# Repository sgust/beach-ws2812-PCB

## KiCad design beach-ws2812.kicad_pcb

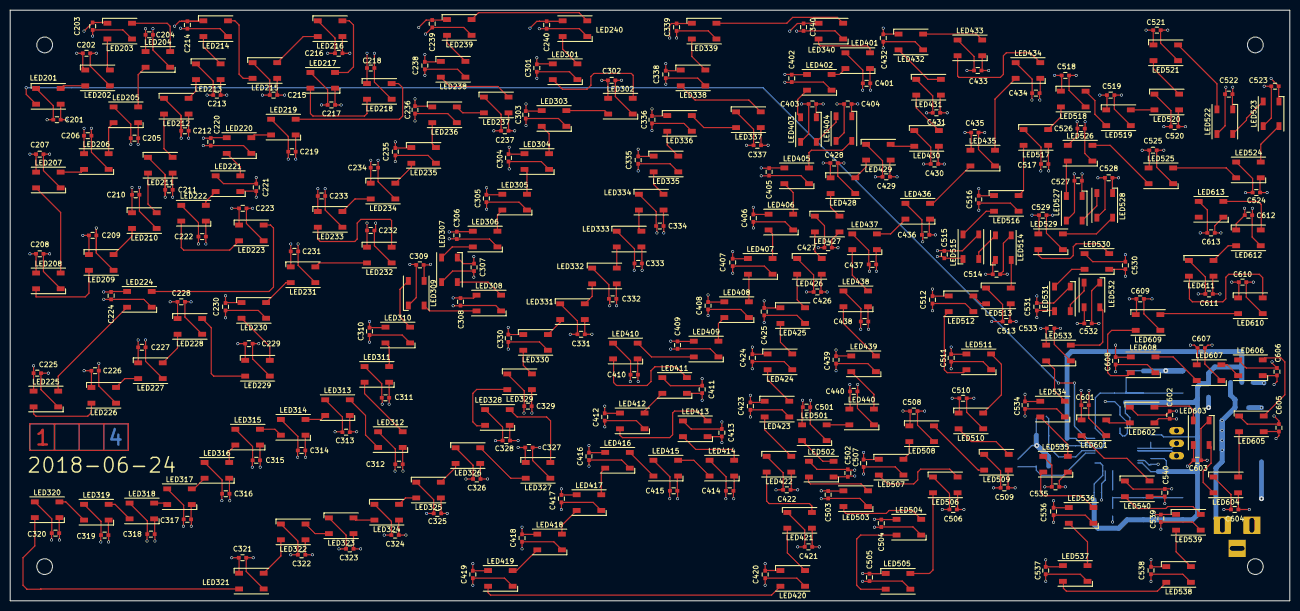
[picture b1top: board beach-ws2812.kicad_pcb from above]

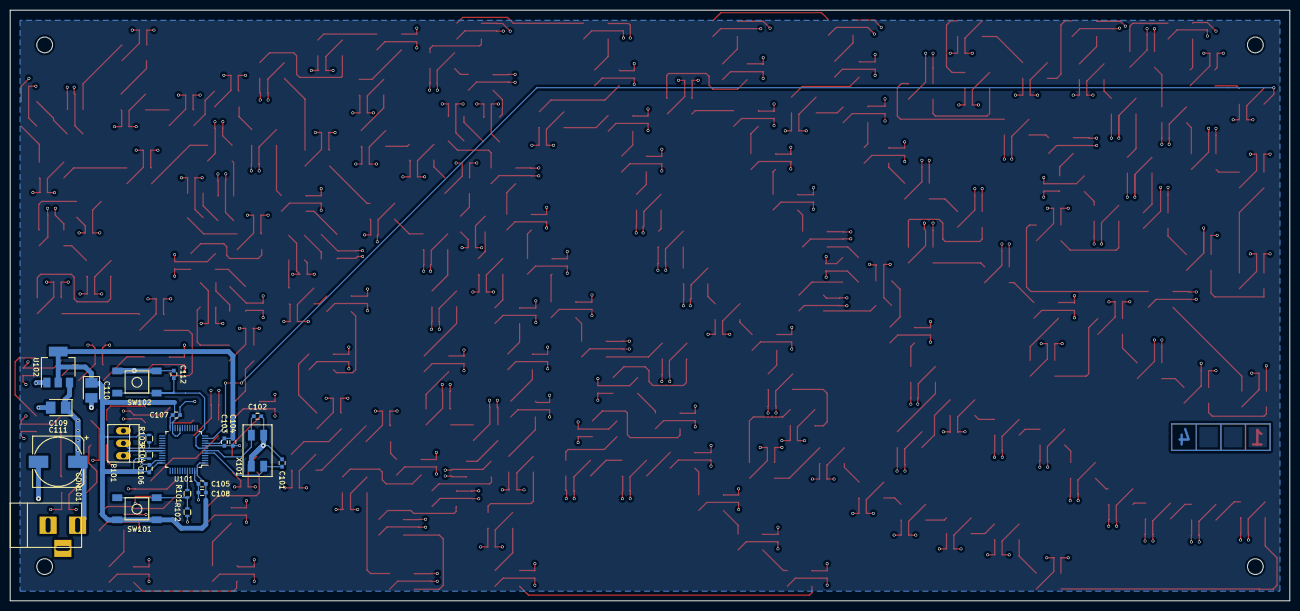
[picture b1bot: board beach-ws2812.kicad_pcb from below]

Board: 4 copper layers, 260.0 x 120.0 mm, 373 parts (23 on the bottom side), 183 nets.

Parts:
C101, C102: 15pF; C_0603
C103: 10nF; C_0603
C104: 1µF; C_0603
C105, C106, C107, C112, C201, C202, C203, C204, C205, C206, C207, C208, C209, C210, C211, C212, C213, C214, C215, C216, C217, C218, C219, C220, C221, C222, C223, C224, C225, C226, C227, C228, C229, C230, C231, C232, C233, C234, C235, C236, C237, C238, C239, C240, C301, C302, C303, C304, C305, C306, C307, C308, C309, C310, C311, C312, C313, C314, C315, C316, C317, C318, C319, C320, C321, C322, C323, C324, C325, C326, C327, C328, C329, C330, C331, C332, C333, C334, C335, C336, C337, C338, C339, C340, C401, C402, C403, C404, C405, C406, C407, C408, C409, C410, C411, C412, C413, C414, C415, C416, C417, C418, C419, C420, C421, C422, C423, C424, C425, C426, C427, C428, C429, C430, C431, C432, C433, C434, C435, C436, C437, C438, C439, C440, C501, C502, C503, C504, C505, C506, C507, C508, C509, C510, C511, C512, C513, C514, C515, C516, C517, C518, C519, C520, C521, C522, C523, C524, C525, C526, C527, C528, C529, C530, C531, C532, C533, C534, C535, C536, C537, C538, C539, C540, C601, C602, C603, C604, C605, C606, C607, C608, C609, C610, C611, C612, C613: 100nF; C_0603
C108: 4.7µF; C_0603
C109, C110: 10µF/16V; Tantalum_Case-B_EIA-3528-21_Reflow
C111: 1000µF/16V; c_elec_10x10
CON101: BARREL_JACK
HOLE1, HOLE2, HOLE3, HOLE4: MountingHole_3.2mm_M3
LED201, LED202, LED203, LED204, LED205, LED206, LED207, LED208, LED209, LED210, LED211, LED212, LED213, LED214, LED215, LED216, LED217, LED218, LED219, LED220, LED221, LED222, LED223, LED224, LED225, LED226, LED227, LED228, LED229, LED230, LED231, LED232, LED233, LED234, LED235, LED236, LED237, LED238, LED239, LED240, LED301, LED302, LED303, LED304, LED305, LED306, LED307, LED308, LED309, LED310, LED311, LED312, LED313, LED314, LED315, LED316, LED317, LED318, LED319, LED320, LED321, LED322, LED323, LED324, LED325, LED326, LED327, LED328, LED329, LED330, LED331, LED332, LED333, LED334, LED335, LED336, LED337, LED338, LED339, LED340, LED401, LED402, LED403, LED404, LED405, LED406, LED407, LED408, LED409, LED410, LED411, LED412, LED413, LED414, LED415, LED416, LED417, LED418, LED419, LED420, LED421, LED422, LED423, LED424, LED425, LED426, LED427, LED428, LED429, LED430, LED431, LED432, LED433, LED434, LED435, LED436, LED437, LED438, LED439, LED440, LED501, LED502, LED503, LED504, LED505, LED506, LED507, LED508, LED509, LED510, LED511, LED512, LED513, LED514, LED515, LED516, LED517, LED518, LED519, LED520, LED521, LED522, LED523, LED524, LED525, LED526, LED527, LED528, LED529, LED530, LED531, LED532, LED533, LED534, LED535, LED536, LED537, LED538, LED539, LED540, LED601, LED602, LED603, LED604, LED605, LED606, LED607, LED608, LED609, LED610, LED611, LED612, LED613: WS2812B; LED_WS2812B-PLCC4
P101: CONN_01X03; PINHEAD1-3
R101: 10K; R_0603
R102: 1K; R_0603
R103, R104: 100K; R_0603
SW101, SW102: Pushbutton; SMD_SWITCH_6x6_LSG
U101: STM32F103C(8-B)Tx; TQFP-48_7x7mm_Pitch0.5mm
U102: LM1117-3.3; SOT-223
X101: 8MHz; Euroquartz_MQ

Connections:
+3V3: C103.1, C104.1, C105.1, C106.1, C107.1, C108.1, C110.1, R103.1, R104.1, SW101.1, SW101.2, U101.1, U101.9, U101.24, U101.36, U101.48, U102.2, U102.4
+5V: C109.1, C111.1, C201.1, C202.1, C203.1, C204.1, C205.1, C206.1, C207.1, C208.1, C209.1, C210.1, C211.1, C212.1, C213.1, C214.1, C215.1, C216.1, C217.1, C218.1, C219.1, C220.1, C221.1, C222.1, C223.1, C224.1, C225.1, C226.1, C227.1, C228.1, C229.1, C230.1, C231.1, C232.1, C233.1, C234.1, C235.1, C236.1, C237.1, C238.1, C239.1, C240.1, C301.1, C302.1, C303.1, C304.1, C305.1, C306.1, C307.1, C308.1, C309.1, C310.1, C311.1, C312.1, C313.1, C314.1, C315.1, C316.1, C317.1, C318.1, C319.1, C320.1, C321.1, C322.1, C323.1, C324.1, C325.1, C326.1, C327.1, C328.1, C329.1, C330.1, C331.1, C332.1, C333.1, C334.1, C335.1, C336.1, C337.1, C338.1, C339.1, C340.1, C401.1, C402.1, C403.1, C404.1, C405.1, C406.1, C407.1, C408.1, C409.1, C410.1, C411.1, C412.1, C413.1, C414.1, C415.1, C416.1, C417.1, C418.1, C419.1, C420.1, C421.1, C422.1, C423.1, C424.1, C425.1, C426.1, C427.1, C428.1, C429.1, C430.1, C431.1, C432.1, C433.1, C434.1, C435.1, C436.1, C437.1, C438.1, C439.1, C440.1, C501.1, C502.1, C503.1, C504.1, C505.1, C506.1, C507.1, C508.1, C509.1, C510.1, C511.1, C512.1, C513.1, C514.1, C515.1, C516.1, C517.1, C518.1, C519.1, C520.1, C521.1, C522.1, C523.1, C524.1, C525.1, C526.1, C527.1, C528.1, C529.1, C530.1, C531.1, C532.1, C533.1, C534.1, C535.1, C536.1, C537.1, C538.1, C539.1, C540.1, C601.1, C602.1, C603.1, C604.1, C605.1, C606.1, C607.1, C608.1, C609.1, C610.1, C611.1, C612.1, C613.1, CON101.1, LED201.1, LED202.1, LED203.1, LED204.1, LED205.1, LED206.1, LED207.1, LED208.1, LED209.1, LED210.1, LED211.1, LED212.1, LED213.1, LED214.1, LED215.1, LED216.1, LED217.1, LED218.1, LED219.1, LED220.1, LED221.1, LED222.1, LED223.1, LED224.1, LED225.1, LED226.1, LED227.1, LED228.1, LED229.1, LED230.1, LED231.1, LED232.1, LED233.1, LED234.1, LED235.1, LED236.1, LED237.1, LED238.1, LED239.1, LED240.1, LED301.1, LED302.1, LED303.1, LED304.1, LED305.1, LED306.1, LED307.1, LED308.1, LED309.1, LED310.1, LED311.1, LED312.1, LED313.1, LED314.1, LED315.1, LED316.1, LED317.1, LED318.1, LED319.1, LED320.1, LED321.1, LED322.1, LED323.1, LED324.1, LED325.1, LED326.1, LED327.1, LED328.1, LED329.1, LED330.1, LED331.1, LED332.1, LED333.1, LED334.1, LED335.1, LED336.1, LED337.1, LED338.1, LED339.1, LED340.1, LED401.1, LED402.1, LED403.1, LED404.1, LED405.1, LED406.1, LED407.1, LED408.1, LED409.1, LED410.1, LED411.1, LED412.1, LED413.1, LED414.1, LED415.1, LED416.1, LED417.1, LED418.1, LED419.1, LED420.1, LED421.1, LED422.1, LED423.1, LED424.1, LED425.1, LED426.1, LED427.1, LED428.1, LED429.1, LED430.1, LED431.1, LED432.1, LED433.1, LED434.1, LED435.1, LED436.1, LED437.1, LED438.1, LED439.1, LED440.1, LED501.1, LED502.1, LED503.1, LED504.1, LED505.1, LED506.1, LED507.1, LED508.1, LED509.1, LED510.1, LED511.1, LED512.1, LED513.1, LED514.1, LED515.1, LED516.1, LED517.1, LED518.1, LED519.1, LED520.1, LED521.1, LED522.1, LED523.1, LED524.1, LED525.1, LED526.1, LED527.1, LED528.1, LED529.1, LED530.1, LED531.1, LED532.1, LED533.1, LED534.1, LED535.1, LED536.1, LED537.1, LED538.1, LED539.1, LED540.1, LED601.1, LED602.1, LED603.1, LED604.1, LED605.1, LED606.1, LED607.1, LED608.1, LED609.1, LED610.1, LED611.1, LED612.1, LED613.1, U102.3
GND: C101.2, C102.2, C103.2, C104.2, C105.2, C106.2, C107.2, C108.2, C109.2, C110.2, C111.2, C112.1, C201.2, C202.2, C203.2, C204.2, C205.2, C206.2, C207.2, C208.2, C209.2, C210.2, C211.2, C212.2, C213.2, C214.2, C215.2, C216.2, C217.2, C218.2, C219.2, C220.2, C221.2, C222.2, C223.2, C224.2, C225.2, C226.2, C227.2, C228.2, C229.2, C230.2, C231.2, C232.2, C233.2, C234.2, C235.2, C236.2, C237.2, C238.2, C239.2, C240.2, C301.2, C302.2, C303.2, C304.2, C305.2, C306.2, C307.2, C308.2, C309.2, C310.2, C311.2, C312.2, C313.2, C314.2, C315.2, C316.2, C317.2, C318.2, C319.2, C320.2, C321.2, C322.2, C323.2, C324.2, C325.2, C326.2, C327.2, C328.2, C329.2, C330.2, C331.2, C332.2, C333.2, C334.2, C335.2, C336.2, C337.2, C338.2, C339.2, C340.2, C401.2, C402.2, C403.2, C404.2, C405.2, C406.2, C407.2, C408.2, C409.2, C410.2, C411.2, C412.2, C413.2, C414.2, C415.2, C416.2, C417.2, C418.2, C419.2, C420.2, C421.2, C422.2, C423.2, C424.2, C425.2, C426.2, C427.2, C428.2, C429.2, C430.2, C431.2, C432.2, C433.2, C434.2, C435.2, C436.2, C437.2, C438.2, C439.2, C440.2, C501.2, C502.2, C503.2, C504.2, C505.2, C506.2, C507.2, C508.2, C509.2, C510.2, C511.2, C512.2, C513.2, C514.2, C515.2, C516.2, C517.2, C518.2, C519.2, C520.2, C521.2, C522.2, C523.2, C524.2, C525.2, C526.2, C527.2, C528.2, C529.2, C530.2, C531.2, C532.2, C533.2, C534.2, C535.2, C536.2, C537.2, C538.2, C539.2, C540.2, C601.2, C602.2, C603.2, C604.2, C605.2, C606.2, C607.2, C608.2, C609.2, C610.2, C611.2, C612.2, C613.2, CON101.2, CON101.3, LED201.3, LED202.3, LED203.3, LED204.3, LED205.3, LED206.3, LED207.3, LED208.3, LED209.3, LED210.3, LED211.3, LED212.3, LED213.3, LED214.3, LED215.3, LED216.3, LED217.3, LED218.3, LED219.3, LED220.3, LED221.3, LED222.3, LED223.3, LED224.3, LED225.3, LED226.3, LED227.3, LED228.3, LED229.3, LED230.3, LED231.3, LED232.3, LED233.3, LED234.3, LED235.3, LED236.3, LED237.3, LED238.3, LED239.3, LED240.3, LED301.3, LED302.3, LED303.3, LED304.3, LED305.3, LED306.3, LED307.3, LED308.3, LED309.3, LED310.3, LED311.3, LED312.3, LED313.3, LED314.3, LED315.3, LED316.3, LED317.3, LED318.3, LED319.3, LED320.3, LED321.3, LED322.3, LED323.3, LED324.3, LED325.3, LED326.3, LED327.3, LED328.3, LED329.3, LED330.3, LED331.3, LED332.3, LED333.3, LED334.3, LED335.3, LED336.3, LED337.3, LED338.3, LED339.3, LED340.3, LED401.3, LED402.3, LED403.3, LED404.3, LED405.3, LED406.3, LED407.3, LED408.3, LED409.3, LED410.3, LED411.3, LED412.3, LED413.3, LED414.3, LED415.3, LED416.3, LED417.3, LED418.3, LED419.3, LED420.3, LED421.3, LED422.3, LED423.3, LED424.3, LED425.3, LED426.3, LED427.3, LED428.3, LED429.3, LED430.3, LED431.3, LED432.3, LED433.3, LED434.3, LED435.3, LED436.3, LED437.3, LED438.3, LED439.3, LED440.3, LED501.3, LED502.3, LED503.3, LED504.3, LED505.3, LED506.3, LED507.3, LED508.3, LED509.3, LED510.3, LED511.3, LED512.3, LED513.3, LED514.3, LED515.3, LED516.3, LED517.3, LED518.3, LED519.3, LED520.3, LED521.3, LED522.3, LED523.3, LED524.3, LED525.3, LED526.3, LED527.3, LED528.3, LED529.3, LED530.3, LED531.3, LED532.3, LED533.3, LED534.3, LED535.3, LED536.3, LED537.3, LED538.3, LED539.3, LED540.3, LED601.3, LED602.3, LED603.3, LED604.3, LED605.3, LED606.3, LED607.3, LED608.3, LED609.3, LED610.3, LED611.3, LED612.3, LED613.3, P101.1, R102.2, SW102.3, SW102.4, U101.8, U101.20, U101.23, U101.35, U101.47, U102.1, X101.2, X101.4
LEDDATA: LED201.4, U101.11
LEDDATA2: LED240.2, LED301.4
LEDDATA3: LED340.2, LED401.4
LEDDATA4: LED440.2, LED501.4
LEDDATA5: LED540.2, LED601.4
unnamed: C101.1, U101.5, X101.1
unnamed: C102.1, U101.6, X101.3
unnamed: C112.2, SW102.1, SW102.2, U101.7
unnamed: LED201.2, LED202.4
unnamed: LED202.2, LED203.4
unnamed: LED203.2, LED204.4
unnamed: LED204.2, LED205.4
unnamed: LED205.2, LED206.4
unnamed: LED206.2, LED207.4
unnamed: LED207.2, LED208.4
unnamed: LED208.2, LED209.4
unnamed: LED209.2, LED210.4
unnamed: LED210.2, LED211.4
unnamed: LED211.2, LED212.4
unnamed: LED212.2, LED213.4
unnamed: LED213.2, LED214.4
unnamed: LED214.2, LED215.4
unnamed: LED215.2, LED216.4
unnamed: LED216.2, LED217.4
unnamed: LED217.2, LED218.4
unnamed: LED218.2, LED219.4
unnamed: LED219.2, LED220.4
unnamed: LED220.2, LED221.4
unnamed: LED221.2, LED222.4
unnamed: LED222.2, LED223.4
unnamed: LED223.2, LED224.4
unnamed: LED224.2, LED225.4
unnamed: LED225.2, LED226.4
unnamed: LED226.2, LED227.4
unnamed: LED227.2, LED228.4
unnamed: LED228.2, LED229.4
unnamed: LED229.2, LED230.4
unnamed: LED230.2, LED231.4
unnamed: LED231.2, LED232.4
unnamed: LED232.2, LED233.4
unnamed: LED233.2, LED234.4
unnamed: LED234.2, LED235.4
unnamed: LED235.2, LED236.4
unnamed: LED236.2, LED237.4
unnamed: LED237.2, LED238.4
unnamed: LED238.2, LED239.4
unnamed: LED239.2, LED240.4
unnamed: LED301.2, LED302.4
unnamed: LED302.2, LED303.4
unnamed: LED303.2, LED304.4
unnamed: LED304.2, LED305.4
unnamed: LED305.2, LED306.4
unnamed: LED306.2, LED307.4
unnamed: LED307.2, LED308.4
unnamed: LED308.2, LED309.4
unnamed: LED309.2, LED310.4
unnamed: LED310.2, LED311.4
unnamed: LED311.2, LED312.4
unnamed: LED312.2, LED313.4
unnamed: LED313.2, LED314.4
unnamed: LED314.2, LED315.4
unnamed: LED315.2, LED316.4
unnamed: LED316.2, LED317.4
unnamed: LED317.2, LED318.4
unnamed: LED318.2, LED319.4
unnamed: LED319.2, LED320.4
unnamed: LED320.2, LED321.4
unnamed: LED321.2, LED322.4
unnamed: LED322.2, LED323.4
unnamed: LED323.2, LED324.4
unnamed: LED324.2, LED325.4
unnamed: LED325.2, LED326.4
unnamed: LED326.2, LED327.4
unnamed: LED327.2, LED328.4
unnamed: LED328.2, LED329.4
unnamed: LED329.2, LED330.4
unnamed: LED330.2, LED331.4
unnamed: LED331.2, LED332.4
unnamed: LED332.2, LED333.4
unnamed: LED333.2, LED334.4
unnamed: LED334.2, LED335.4
unnamed: LED335.2, LED336.4
unnamed: LED336.2, LED337.4
unnamed: LED337.2, LED338.4
unnamed: LED338.2, LED339.4
unnamed: LED339.2, LED340.4
unnamed: LED401.2, LED402.4
unnamed: LED402.2, LED403.4
unnamed: LED403.2, LED404.4
unnamed: LED404.2, LED405.4
unnamed: LED405.2, LED406.4
unnamed: LED406.2, LED407.4
unnamed: LED407.2, LED408.4
unnamed: LED408.2, LED409.4
unnamed: LED409.2, LED410.4
unnamed: LED410.2, LED411.4
unnamed: LED411.2, LED412.4
unnamed: LED412.2, LED413.4
unnamed: LED413.2, LED414.4
unnamed: LED414.2, LED415.4
unnamed: LED415.2, LED416.4
unnamed: LED416.2, LED417.4
unnamed: LED417.2, LED418.4
unnamed: LED418.2, LED419.4
unnamed: LED419.2, LED420.4
unnamed: LED420.2, LED421.4
unnamed: LED421.2, LED422.4
unnamed: LED422.2, LED423.4
unnamed: LED423.2, LED424.4
unnamed: LED424.2, LED425.4
unnamed: LED425.2, LED426.4
unnamed: LED426.2, LED427.4
unnamed: LED427.2, LED428.4
unnamed: LED428.2, LED429.4
unnamed: LED429.2, LED430.4
unnamed: LED430.2, LED431.4
unnamed: LED431.2, LED432.4
unnamed: LED432.2, LED433.4
unnamed: LED433.2, LED434.4
unnamed: LED434.2, LED435.4
unnamed: LED435.2, LED436.4
unnamed: LED436.2, LED437.4
unnamed: LED437.2, LED438.4
unnamed: LED438.2, LED439.4
unnamed: LED439.2, LED440.4
unnamed: LED501.2, LED502.4
unnamed: LED502.2, LED503.4
unnamed: LED503.2, LED504.4
unnamed: LED504.2, LED505.4
unnamed: LED505.2, LED506.4
unnamed: LED506.2, LED507.4
unnamed: LED507.2, LED508.4
unnamed: LED508.2, LED509.4
unnamed: LED509.2, LED510.4
unnamed: LED510.2, LED511.4
unnamed: LED511.2, LED512.4
unnamed: LED512.2, LED513.4
unnamed: LED513.2, LED514.4
unnamed: LED514.2, LED515.4
unnamed: LED515.2, LED516.4
unnamed: LED516.2, LED517.4
unnamed: LED517.2, LED518.4
unnamed: LED518.2, LED519.4
unnamed: LED519.2, LED520.4
unnamed: LED520.2, LED521.4
unnamed: LED521.2, LED522.4
unnamed: LED522.2, LED523.4
unnamed: LED523.2, LED524.4
unnamed: LED524.2, LED525.4
unnamed: LED525.2, LED526.4
unnamed: LED526.2, LED527.4
unnamed: LED527.2, LED528.4
unnamed: LED528.2, LED529.4
unnamed: LED529.2, LED530.4
unnamed: LED530.2, LED531.4
unnamed: LED531.2, LED532.4
unnamed: LED532.2, LED533.4
unnamed: LED533.2, LED534.4
unnamed: LED534.2, LED535.4
unnamed: LED535.2, LED536.4
unnamed: LED536.2, LED537.4
unnamed: LED537.2, LED538.4
unnamed: LED538.2, LED539.4
unnamed: LED539.2, LED540.4
unnamed: LED601.2, LED602.4
unnamed: LED602.2, LED603.4
unnamed: LED603.2, LED604.4
unnamed: LED604.2, LED605.4
unnamed: LED605.2, LED606.4
unnamed: LED606.2, LED607.4
unnamed: LED607.2, LED608.4
unnamed: LED608.2, LED609.4
unnamed: LED609.2, LED610.4
unnamed: LED610.2, LED611.4
unnamed: LED611.2, LED612.4
unnamed: LED612.2, LED613.4
unnamed: P101.2, R103.2, U101.30
unnamed: P101.3, R104.2, U101.31
unnamed: R101.1, U101.44
unnamed: R101.2, R102.1, SW101.3, SW101.4

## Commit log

2018-05-01 Initial commit.
2018-05-01 Import library.
2018-05-01 Ignore cache, ignore backup files.
2018-05-05 Started placement (got footprints from usblink project).
2018-05-05 More routing done on CPU.
2018-05-05 Finished routing with only 1 random placed LED.
2018-05-05 Added converted LED position.
2018-05-05 Routed to first LED final position.
2018-05-05 Extra library.
2018-05-05 Now with 16 LEDs placed.
2018-05-06 Routed 40 LEDs.
2018-05-06 80 LEDs placed and routed.
2018-05-06 Now with 120 LEDs routed.
2018-05-06 Ignore pcb backup file.
2018-05-07 Placed 160 LEDs (caps missing for the last 40).
2018-05-08 Routed 160 LEDs.
2018-05-08 Now placed and routed all 173 LEDs.
2018-05-08 Added mounting holes.
2018-05-09 Minor fixes after looking at printout. Added date as version marker.
2018-05-09 Added big copper plane, warning about possible production problem from eurocircuits.
2018-05-21 Changed tantalums on 3.3V regulator to size B.
2018-05-21 Added weak pull-ups to programming RX/TX pins.
2018-05-27 Rotated power connector, now to the side. Updated time stamp.
2018-06-24 Fixed silk screen problems found while building first prototype.
